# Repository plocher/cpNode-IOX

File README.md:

## cpNode IOX

16 bit I2C I/O Expander for MRCS cpNode system

Features
 - 23017 IO Expander
 - local 5v 750mA regulated power for attached accessories
 - 0.100 screw terminals for layout connections
 - I2C address display
 - Daisy chained 7.5c-12v DC unregulated power source feed through

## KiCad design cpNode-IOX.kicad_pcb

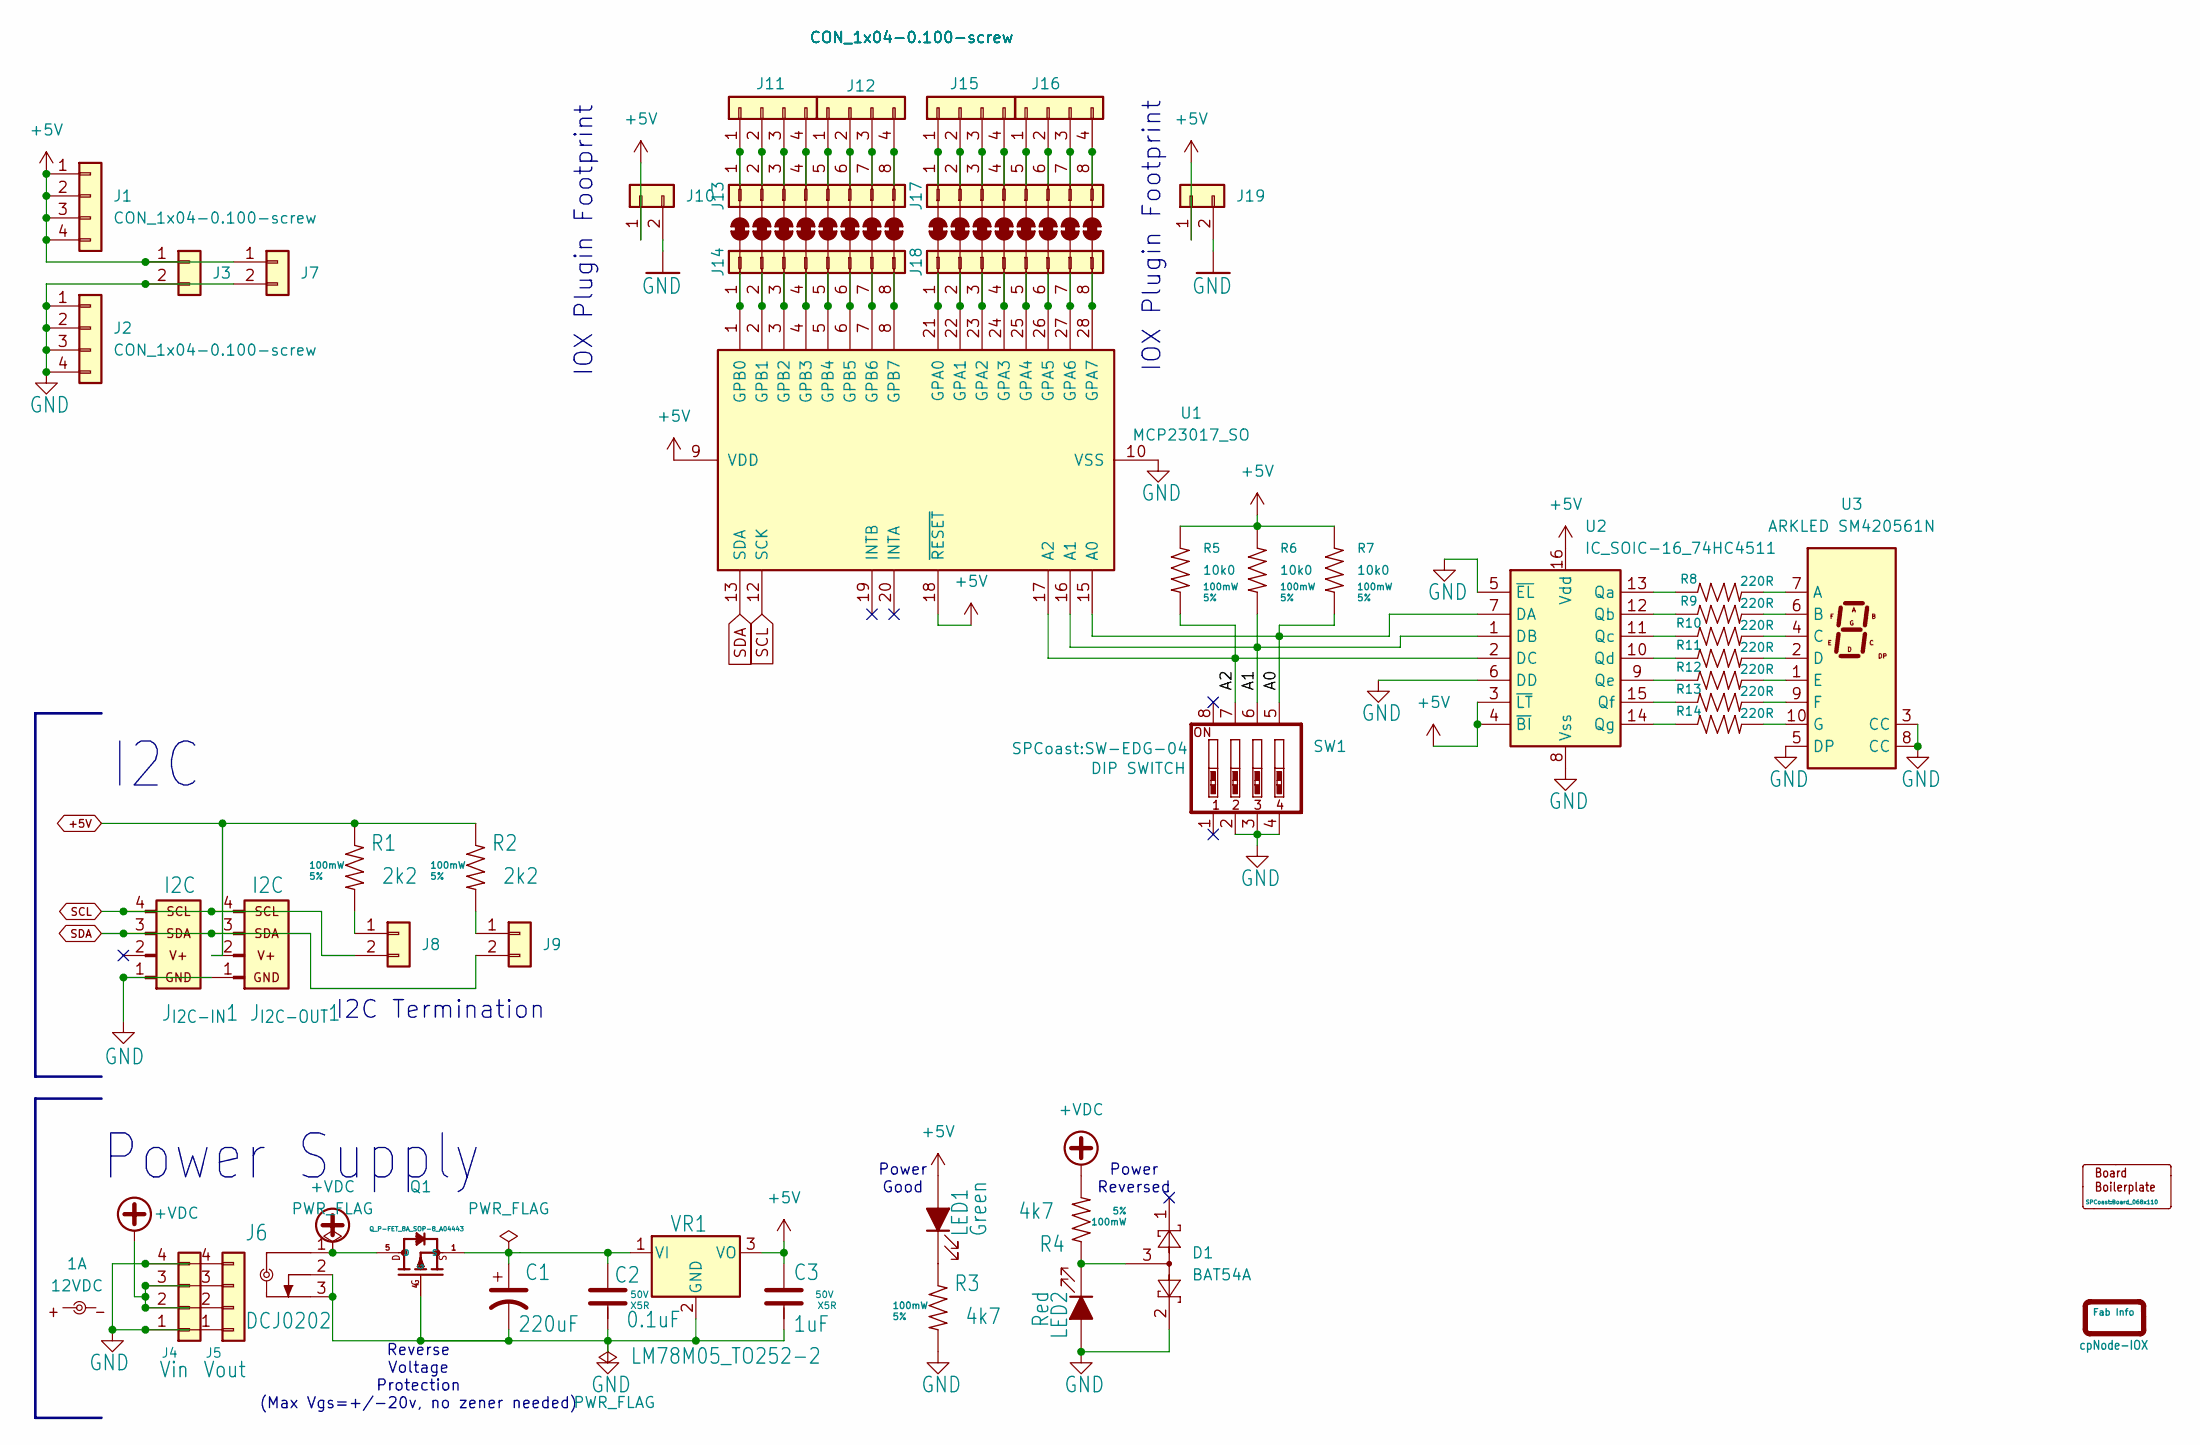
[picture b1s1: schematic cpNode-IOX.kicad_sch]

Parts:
Board1: Board_068x110
C1: 220uF; CP_Elec_8x10
C2: 0.1uF; 0603-CAP; Voltage 50V
C3: 1uF; 0603-CAP; Voltage 50V
D1: BAT54A; SOT-23
DOC1: ${TITLE}; SILK_BoardID
J1, J2: CON_1x04-0.100-screw; PinHeader_1x04_P2.54mm_Vertical
J3, J7, J8, J9, J10, J19: Conn_01x02; PinHeader_1x02_P2.54mm_Vertical
J4: Vin; PinHeader_1x04_P2.54mm_Vertical; LCSC C2691448
J5: Vout; PinHeader_1x04_P2.54mm_Vertical; LCSC C2691448
J6: DCJ0202; BarrelJack_Kycon_KLDX-0202-xC_Horizontal; Voltage 5vDC
J11, J12, J15, J16: CON_1x04-0.100-screw; PinHeader_1x04_P2.54mm_Vertical; LCSC C3816889
J13, J14, J17, J18: Conn_01x08; PinHeader_1x08_P2.54mm_Vertical
J_{I2C-IN}1: I2C; Connector_I2C-0.100_R; LCSC C2691448
J_{I2C-OUT}1: I2C; Connector_I2C-0.100_L; LCSC C2691448
LED1: Green; 0603-LED
LED2: Red; 0603-LED
PWR-LABEL1: 12VDC @1A; SILK_Label-Power_CP
Q1: Q_P-FET_8A_SOP-8_A04443; HTSOP-8-1EP_3.9x4.9mm_P1.27mm_EP2.4x3.2mm
R1, R2: 2k2; 0603-RES; Tolerance 5%
R3, R4: 4k7; 0603-RES; Tolerance 5%
R5, R6, R7: 10k0; 0603-RES; Tolerance 5%
R8, R9, R10, R11, R12, R13, R14: 220R; 0603-RES; Tolerance 5%
SJ1, SJ2, SJ3, SJ4, SJ5, SJ6, SJ7, SJ8, SJ9, SJ10, SJ11, SJ12, SJ13, SJ14, SJ15, SJ16: OFF; SolderJumper-2_P1.3mm_Bridged_RoundedPad1.0x1.5mm
SW1: SW-EDG-04
U1: MCP23017_SO; SOIC-28W_7.5x17.9mm_P1.27mm
U2: IC_SOIC-16_74HC4511; SOIC-16_3.9x9.9mm_P1.27mm
U3: ARKLED SM420561N; D1X8K; LCSC C141367
VR1: LM78M05_TO252-2; TO-252-2; LCSC C347278

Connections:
+5V: C3.1, J1.1, J1.2, J1.3, J1.4, J3.1, J7.1, J10.1, J19.1, J_{I2C-OUT}1.2, LED1.2 (A), R1.1, R2.1, R5.1, R6.1, R7.1, U1.9 (VDD), U1.18 (~RESET), U2.3 (~LT), U2.4 (~BI), U2.16 (Vdd), VR1.3 (VO)
+VDC: J4.2, J4.3, J5.2, J5.3, J6.1, Q1.5 (D), Q1.6 (D), Q1.7 (D), Q1.8 (D), Q1.9 (D), R4.2
/A0: R7.2, SW1.5, U1.15 (A0), U2.7 (DA)
/A1: R6.2, SW1.6, U1.16 (A1), U2.1 (DB)
/A2: R5.2, SW1.7, U1.17 (A2), U2.2 (DC)
GND: C1.2, C2.2, C3.2, D1.2, J2.1, J2.2, J2.3, J2.4, J3.2, J4.1, J4.4, J5.1, J5.4, J6.2, J6.3, J7.2, J10.2, J19.2, J_{I2C-IN}1.1, J_{I2C-OUT}1.1, LED2.2 (A), Q1.4 (G), R3.2, SW1.2, SW1.3, SW1.4, U1.10 (VSS), U2.5 (~EL), U2.6 (DD), U2.8 (Vss), U3.3 (CC), U3.5 (DP), U3.8 (CC), VR1.2 (GND)
unnamed: J8.1, R1.2
unnamed: J9.1, R2.2
unnamed: J11.1, J13.1, SJ1.1 (A)
unnamed: J11.2, J13.2, SJ2.1 (A)
unnamed: J11.3, J13.3, SJ3.1 (A)
unnamed: J11.4, J13.4, SJ4.1 (A)
unnamed: J12.1, J13.5, SJ5.1 (A)
unnamed: J12.2, J13.6, SJ6.1 (A)
unnamed: J12.3, J13.7, SJ7.1 (A)
unnamed: J12.4, J13.8, SJ8.1 (A)
unnamed: J14.1, SJ1.2 (B), U1.1 (GPB0)
unnamed: J14.2, SJ2.2 (B), U1.2 (GPB1)
unnamed: J14.3, SJ3.2 (B), U1.3 (GPB2)
unnamed: J14.4, SJ4.2 (B), U1.4 (GPB3)
unnamed: J14.5, SJ5.2 (B), U1.5 (GPB4)
unnamed: J14.6, SJ6.2 (B), U1.6 (GPB5)
unnamed: J14.7, SJ7.2 (B), U1.7 (GPB6)
unnamed: J14.8, SJ8.2 (B), U1.8 (GPB7)
unnamed: J15.1, J17.1, SJ9.1 (A)
unnamed: J15.2, J17.2, SJ10.1 (A)
unnamed: J15.3, J17.3, SJ11.1 (A)
unnamed: J15.4, J17.4, SJ12.1 (A)
unnamed: J16.1, J17.5, SJ13.1 (A)
unnamed: J16.2, J17.6, SJ14.1 (A)
unnamed: J16.3, J17.7, SJ15.1 (A)
unnamed: J16.4, J17.8, SJ16.1 (A)
unnamed: J18.1, SJ9.2 (B), U1.21 (GPA0)
unnamed: J18.2, SJ10.2 (B), U1.22 (GPA1)
unnamed: J18.3, SJ11.2 (B), U1.23 (GPA2)
unnamed: J18.4, SJ12.2 (B), U1.24 (GPA3)
unnamed: J18.5, SJ13.2 (B), U1.25 (GPA4)
unnamed: J18.6, SJ14.2 (B), U1.26 (GPA5)
unnamed: J18.7, SJ15.2 (B), U1.27 (GPA6)
unnamed: J18.8, SJ16.2 (B), U1.28 (GPA7)
unnamed: LED1.1 (K), R3.1
unnamed: D1.3, LED2.1 (K), R4.1
unnamed: R8.1, U2.13 (Qa)
unnamed: R9.1, U2.12 (Qb)
unnamed: R10.1, U2.11 (Qc)
unnamed: R11.1, U2.10 (Qd)
unnamed: R12.1, U2.9 (Qe)
unnamed: R13.1, U2.15 (Qf)
unnamed: R14.1, U2.14 (Qg)
unnamed: R8.2, U3.7 (A)
unnamed: R9.2, U3.6 (B)
unnamed: R10.2, U3.4 (C)
unnamed: R11.2, U3.2 (D)
unnamed: R12.2, U3.1 (E)
unnamed: R13.2, U3.9 (F)
unnamed: R14.2, U3.10 (G)
unnamed: C1.1, C2.1, Q1.1 (S), Q1.2 (S), Q1.3 (S), VR1.1 (VI)
SCL: J8.2, J_{I2C-IN}1.4, J_{I2C-OUT}1.4, U1.12 (SCK)
SDA: J9.2, J_{I2C-IN}1.3, J_{I2C-OUT}1.3, U1.13 (SDA)

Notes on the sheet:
Power Good
Power Reversed
I2C
IOX Plugin Footprint
I2C Termination
Reverse Voltage Protection (Max Vgs=+/-20v, no zener needed)
Power Supply

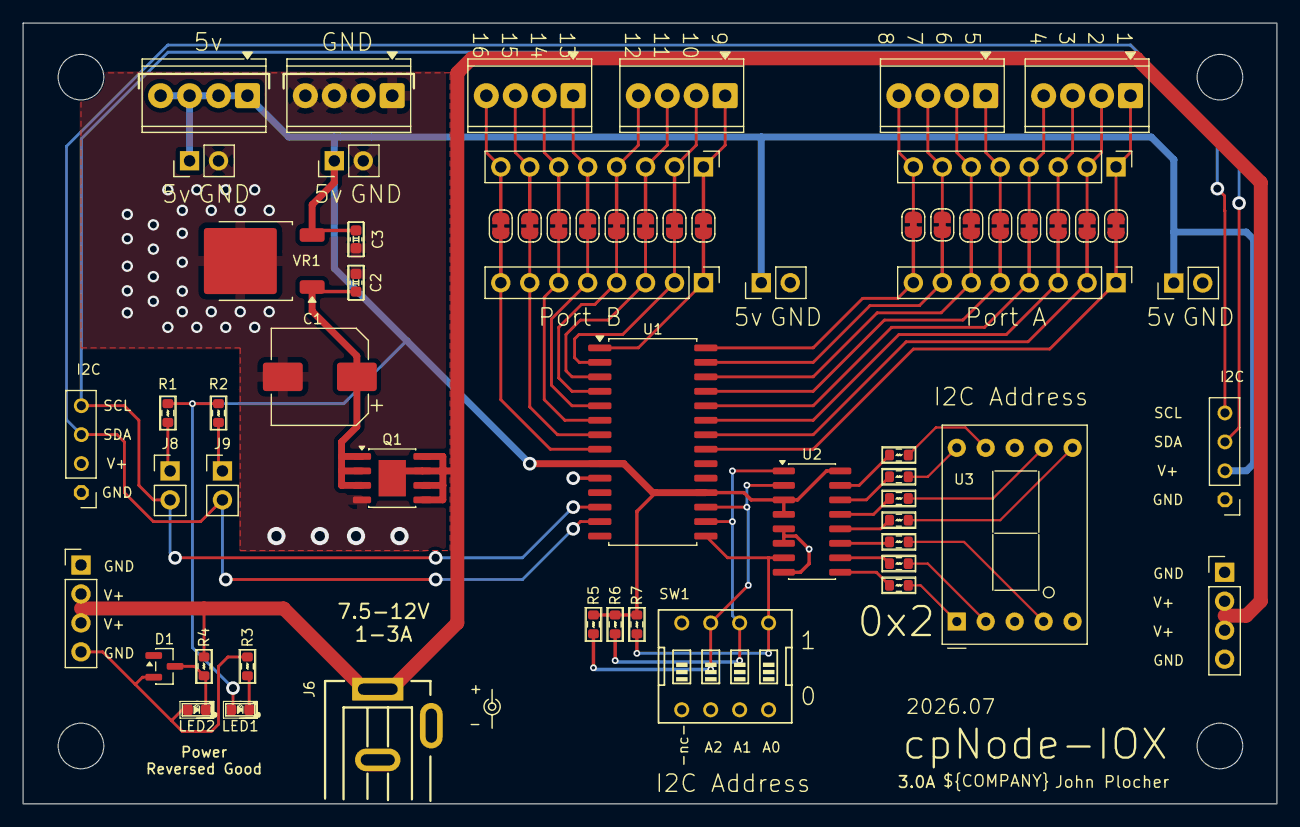
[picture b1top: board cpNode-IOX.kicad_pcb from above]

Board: 2 copper layers, 110.0 x 68.5 mm, 66 parts (0 on the bottom side), 59 nets.
